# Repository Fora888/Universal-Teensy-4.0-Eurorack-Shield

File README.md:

# Universal-Teensy-4.0-Eurorack-Shield
This PCB is designed to piggyback onto a perfboard, to eneable easy designing and building of custom DSP based eurorack modules. It features two 24-bit audio input and two 24-bit audio output channels. The corresponding DAC and ADC are wired up to easily work with the PJRC audio library. 

## Components
All components minus the Teensy 4.0 microcontroller and PCB can be easily ordered with the mouser project below
https://www.mouser.com/ProjectManager/ProjectDetail.aspx?AccessID=7126760366

The PCB can be ordered at a PCB manufacturer of your choice. I ordered mine at Aisler.

## Building Notes
I recommend to reflow solder this board, since most pads are really close to eachother. If you however choose to handsolder, my advice is to go from smallest to largest component.

The headers on the teensy need to be on the same side as the USB port, so that the USB port faces towards the PCB when mounted. This is done to allow utilisation of the backside pins of the Teensy. There are also 5V and GND markings on the PCB to ensure correct orientation.

## Schematic

## 3DRender

## Example Modules
There are currently no working examples. I am however working on a wavetable module based on this board. I'll add it as soon as it's finished.

## Disclaimer
The Updated PCB has yet to be build and is therefore not guaranteed to work. The last commit that was build and tested is [df5ed19](https://github.com/Fora888/Universal-Teensy-4.0-Eurorack-Shield/tree/df5ed198294865db2b968ab182dcd4eb55e7e81e)

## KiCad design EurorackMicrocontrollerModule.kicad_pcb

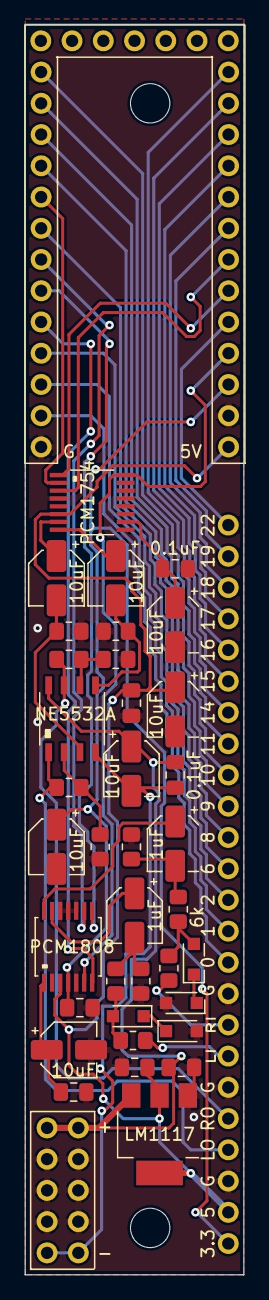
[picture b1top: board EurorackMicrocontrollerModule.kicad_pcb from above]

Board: 2 copper layers, 17.8 x 101.6 mm, 41 parts (1 on the bottom side), 47 nets.

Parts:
C1, C2, C4, C5, C7, C11, C15: 10uF; CP_Elec_4x4.5
C3, C6, C10, C12, C16: 0.1uF; C_0805_2012Metric_Pad1.18x1.45mm_HandSolder
C8, C9: 1uF; CP_Elec_4x4.5
C13: 10uF; C_0805_2012Metric_Pad1.18x1.45mm_HandSolder
C14: 22uF; C_0805_2012Metric_Pad1.18x1.45mm_HandSolder
D1, D2, D3, D4: 4.7V; D_SOD-323_HandSoldering
J1: Teensy4.0_Pins_Right; PinSocket_1x13_P2.54mm_Vertical
J2: Teensy4.0_Pins_Left; PinSocket_1x13_P2.54mm_Vertical
J3: Conn_01x24_Male; PinHeader_1x24_P2.54mm_Vertical
J4: Conn_02x05_Counter_Clockwise; PinHeader_2x05_P2.54mm_Vertical
J5: Teensy4.0_Pins_Top; PinSocket_1x07_P2.54mm_Vertical
OpAmp1: NE5532A; NE5532AD
R1, R3: 10k; R_0805_2012Metric_Pad1.20x1.40mm_HandSolder
R2, R4: 15k; R_0805_2012Metric_Pad1.20x1.40mm_HandSolder
R5, R6: 5k; R_0805_2012Metric_Pad1.20x1.40mm_HandSolder
R7, R10: 3k; R_0805_2012Metric_Pad1.20x1.40mm_HandSolder
R8, R11: 6k; R_0805_2012Metric_Pad1.20x1.40mm_HandSolder
R9, R12: 1k; R_0805_2012Metric_Pad1.20x1.40mm_HandSolder
U1: PCM1754DBQ
U2: PCM1808PW
U3: LM1117-5.0; SOT-223-3_TabPin2

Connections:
+3.3V: C11.1, C12.1, J2.3.3V, J3.1, U2.4 (VDD)
+5V: C5.1, C6.1, C14.1, J2.Vin, J3.2, U1.6 (VCC), U2.3 (VCC), U3.2 (VO)
+12V: C1.1, C3.1, C13.1, J4.5, J4.6, OpAmp1.8 (VCC+), U3.3 (VI)
-12V: C1.2, C3.2, J4.1, J4.10, OpAmp1.4 (VCC-)
/5VPPAudioOutL: J3.4, OpAmp1.1 (1OUT), R2.2
/5VPPAudioOutR: J3.5, OpAmp1.7 (2OUT), R4.1
/LAudioIn: J3.7, R9.2
/RAudioIn: J3.8, R12.2
/Teensy_Pin_0: J1.0 (Pin_2), J3.10
/Teensy_Pin_1: J1.1 (Pin_3), J3.11
/Teensy_Pin_2: J1.2 (Pin_4), J3.12
/Teensy_Pin_6: J1.6 (Pin_8), J3.13
/Teensy_Pin_8: J1.8 (Pin_10), J3.14
/Teensy_Pin_9: J1.9 (Pin_11), J3.15
/Teensy_Pin_10: J1.10 (Pin_12), J3.16
/Teensy_Pin_11: J1.11 (Pin_13), J3.17
/Teensy_Pin_14: J2.14 (Pin_1), J3.18
/Teensy_Pin_15: J2.15 (Pin_2), J3.19
/Teensy_Pin_16: J2.16 (Pin_3), J3.20
/Teensy_Pin_17: J2.17 (Pin_4), J3.21
/Teensy_Pin_18: J2.18 (Pin_5), J3.22
/Teensy_Pin_19: J2.19 (Pin_6), J3.23
/Teensy_Pin_22: J2.22 (PWM), J3.24
GND: C5.2, C6.2, C7.2, C10.1, C11.2, C12.2, C13.2, C14.2, C15.2, C16.1, D2.2 (A), D4.2 (A), J1.GND, J2.GND, J3.3, J3.6, J3.9, J4.2, J4.3, J4.4, J4.7, J4.8, J4.9, R1.1, R3.2, R5.1, R6.1, R7.1, R10.1, U1.4 (DGND), U1.9 (AGND), U1.12 (TEST), U1.13 (DEMP), U1.14 (MUTE), U1.15 (FMT), U2.2 (AGND), U2.5 (DGND), U2.10 (MD0), U2.11 (MD1), U2.12 (FMT), U3.1 (ADJ)
unnamed: C2.1, U1.7 (VOUTL)
unnamed: C2.2, OpAmp1.3 (1IN+), R5.2
unnamed: C4.1, U1.8 (VOUTR)
unnamed: C4.2, OpAmp1.5 (2IN+), R6.2
unnamed: C8.1, U2.14 (VINR)
unnamed: C8.2, R10.2, R11.1
unnamed: C9.1, U2.13 (VINL)
unnamed: C9.2, R7.2, R8.1
unnamed: C7.1, C10.2, U2.1 (VREF)
unnamed: C15.1, C16.2, U1.10 (VCOM)
unnamed: D1.1 (K), D2.1 (K)
unnamed: D1.2 (A), R8.2, R9.1
unnamed: D3.1 (K), D4.1 (K)
unnamed: D3.2 (A), R11.2, R12.1
unnamed: J1.3 (Pin_5), U2.7 (LRCK)
unnamed: J1.4 (Pin_6), U2.8 (BCK)
unnamed: J1.5 (Pin_7), U2.9 (DOUT)
unnamed: J1.7 (Pin_9), U1.2 (DATA)
unnamed: J2.20 (LRCKLK1), U1.3 (LRCK)
unnamed: J2.21 (BCLK1), U1.1 (BCK)
unnamed: J2.23 (MCLK1), U1.16 (SCK), U2.6 (SCKI)
unnamed: OpAmp1.2 (1IN-), R1.2, R2.1
unnamed: OpAmp1.6 (2IN-), R3.1, R4.2

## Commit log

2022-08-28 images for Readme
2022-09-01 Changed LDO pad layout to a more common one
2022-09-22 Shortened PCB and moved top Screw hole; Added pin labels; Moved capacitor near power plug
2022-09-22 updated render

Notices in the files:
parts and their libraries:
Copyright 2021 Accelerated Designs. All rights reserved.
